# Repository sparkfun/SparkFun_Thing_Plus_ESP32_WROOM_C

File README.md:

SparkFun Thing Plus - ESP32 WROOM (USB-C)
========================================

*[SparkFun Thing Plus - ESP32 WROOM (USB-C) (WRL-20168)](https://www.sparkfun.com/products/20168)*

The [SparkFun Thing Plus - ESP32 WROOM (USB-C)](https://www.sparkfun.com/products/20168) is a comprehensive development platform for [Espressif's ESP32](https://espressif.com/en/products/hardware/esp32/overview). Thanks to the onboard ESP32 WROOM module, the SparkFun Thing Plus features 16MB of flash memory, 520kB of internal SRAM, an integrated 802.11 BGN WiFi transceiver and dual-mode Bluetooth capabilities, a JST connector to plug in a LiPo battery, a Qwiic connector, and 21 I/O pins. Add to that a rich set of peripherals ranging from capacitive touch sensors, Hall sensors, SD card interface, Ethernet, high-speed SPIs, UARTs, I2S, and I<sup>2</sup>C.

We took all the good from the original [ESP32 Thing Plus](https://www.sparkfun.com/products/15663) and sprinkled on some more. We upgraded to a USB-C connector that provides up to 2A of power, added a fuel gauge IC that will make sure you know your battery levels, included a NeoPixel (WS2812C) RGB LED is the perfect multi-status indicator, and threw a microSD connector on the back! Oh, and the new taller reset and boot buttons are **so** much easier to push! We even dedicated a voltage regulator to the Qwiic connector, which enables software power control to the Qwiic bus - great for low power logging!

Repository Contents
-------------------

* **[/Hardware](/Hardware/)** - KiCad design files (.kicad_sch, .kicad_pcb). Parts come from the [SparkFun KiCad Libraries](https://github.com/sparkfun/SparkFun-KiCad-Libraries)
* **[/Documents](/Documents/)** - Design notes: pin map, design calculations, BOM changes
* **[/Firmware](/Firmware/)** - Example sketches demonstrating extra peripherals

Documentation
--------------
* **[Hookup Guide](https://learn.sparkfun.com/tutorials/2353)** - Hookup guide for the ESP32 Thing Plus (USB-C).
* **[SparkFun Graphical Datasheets](https://github.com/sparkfun/Graphical_Datasheets)** -Graphical Datasheets for various SparkFun products.

Product Versions
----------------
* ESP32 Thing Plus (USB-C variant)
  * [WRL-20168](https://www.sparkfun.com/products/20168) - v5.0, ESP32-WROOM-32E-N16R2 module (16MB flash, 2MB PSRAM). Header RX moves to IO17 and TX to IO1 (UART0) because IO16 is used by the PSRAM. Design files moved from Eagle to KiCad.
  * [WRL-20168](https://www.sparkfun.com/products/20168) - v1.0, Initial Release
  * [SPX-18018](https://www.sparkfun.com/products/18018) - SparkX Release
* ESP32 Thing Plus
  * [WRL-17381](https://www.sparkfun.com/products/17381) (u.FL variant) - v1.0, Initial Release
  * [WRL-15663](https://www.sparkfun.com/products/15663)- v2.0, Slight hardware update that includes a 10&ohm; series resistor between VUSB and CP2102
  * [WRL-14689](https://www.sparkfun.com/products/14689)- v1.0, Initial Release

License Information
-------------------

This product is _**open source**_! 

Please review the LICENSE.md file for license information. 

If you have any questions or concerns on licensing, please contact technical support on our [SparkFun forums](https://forum.sparkfun.com/viewforum.php?f=152).

Distributed as-is; no warranty is given.

- Your friends at SparkFun.

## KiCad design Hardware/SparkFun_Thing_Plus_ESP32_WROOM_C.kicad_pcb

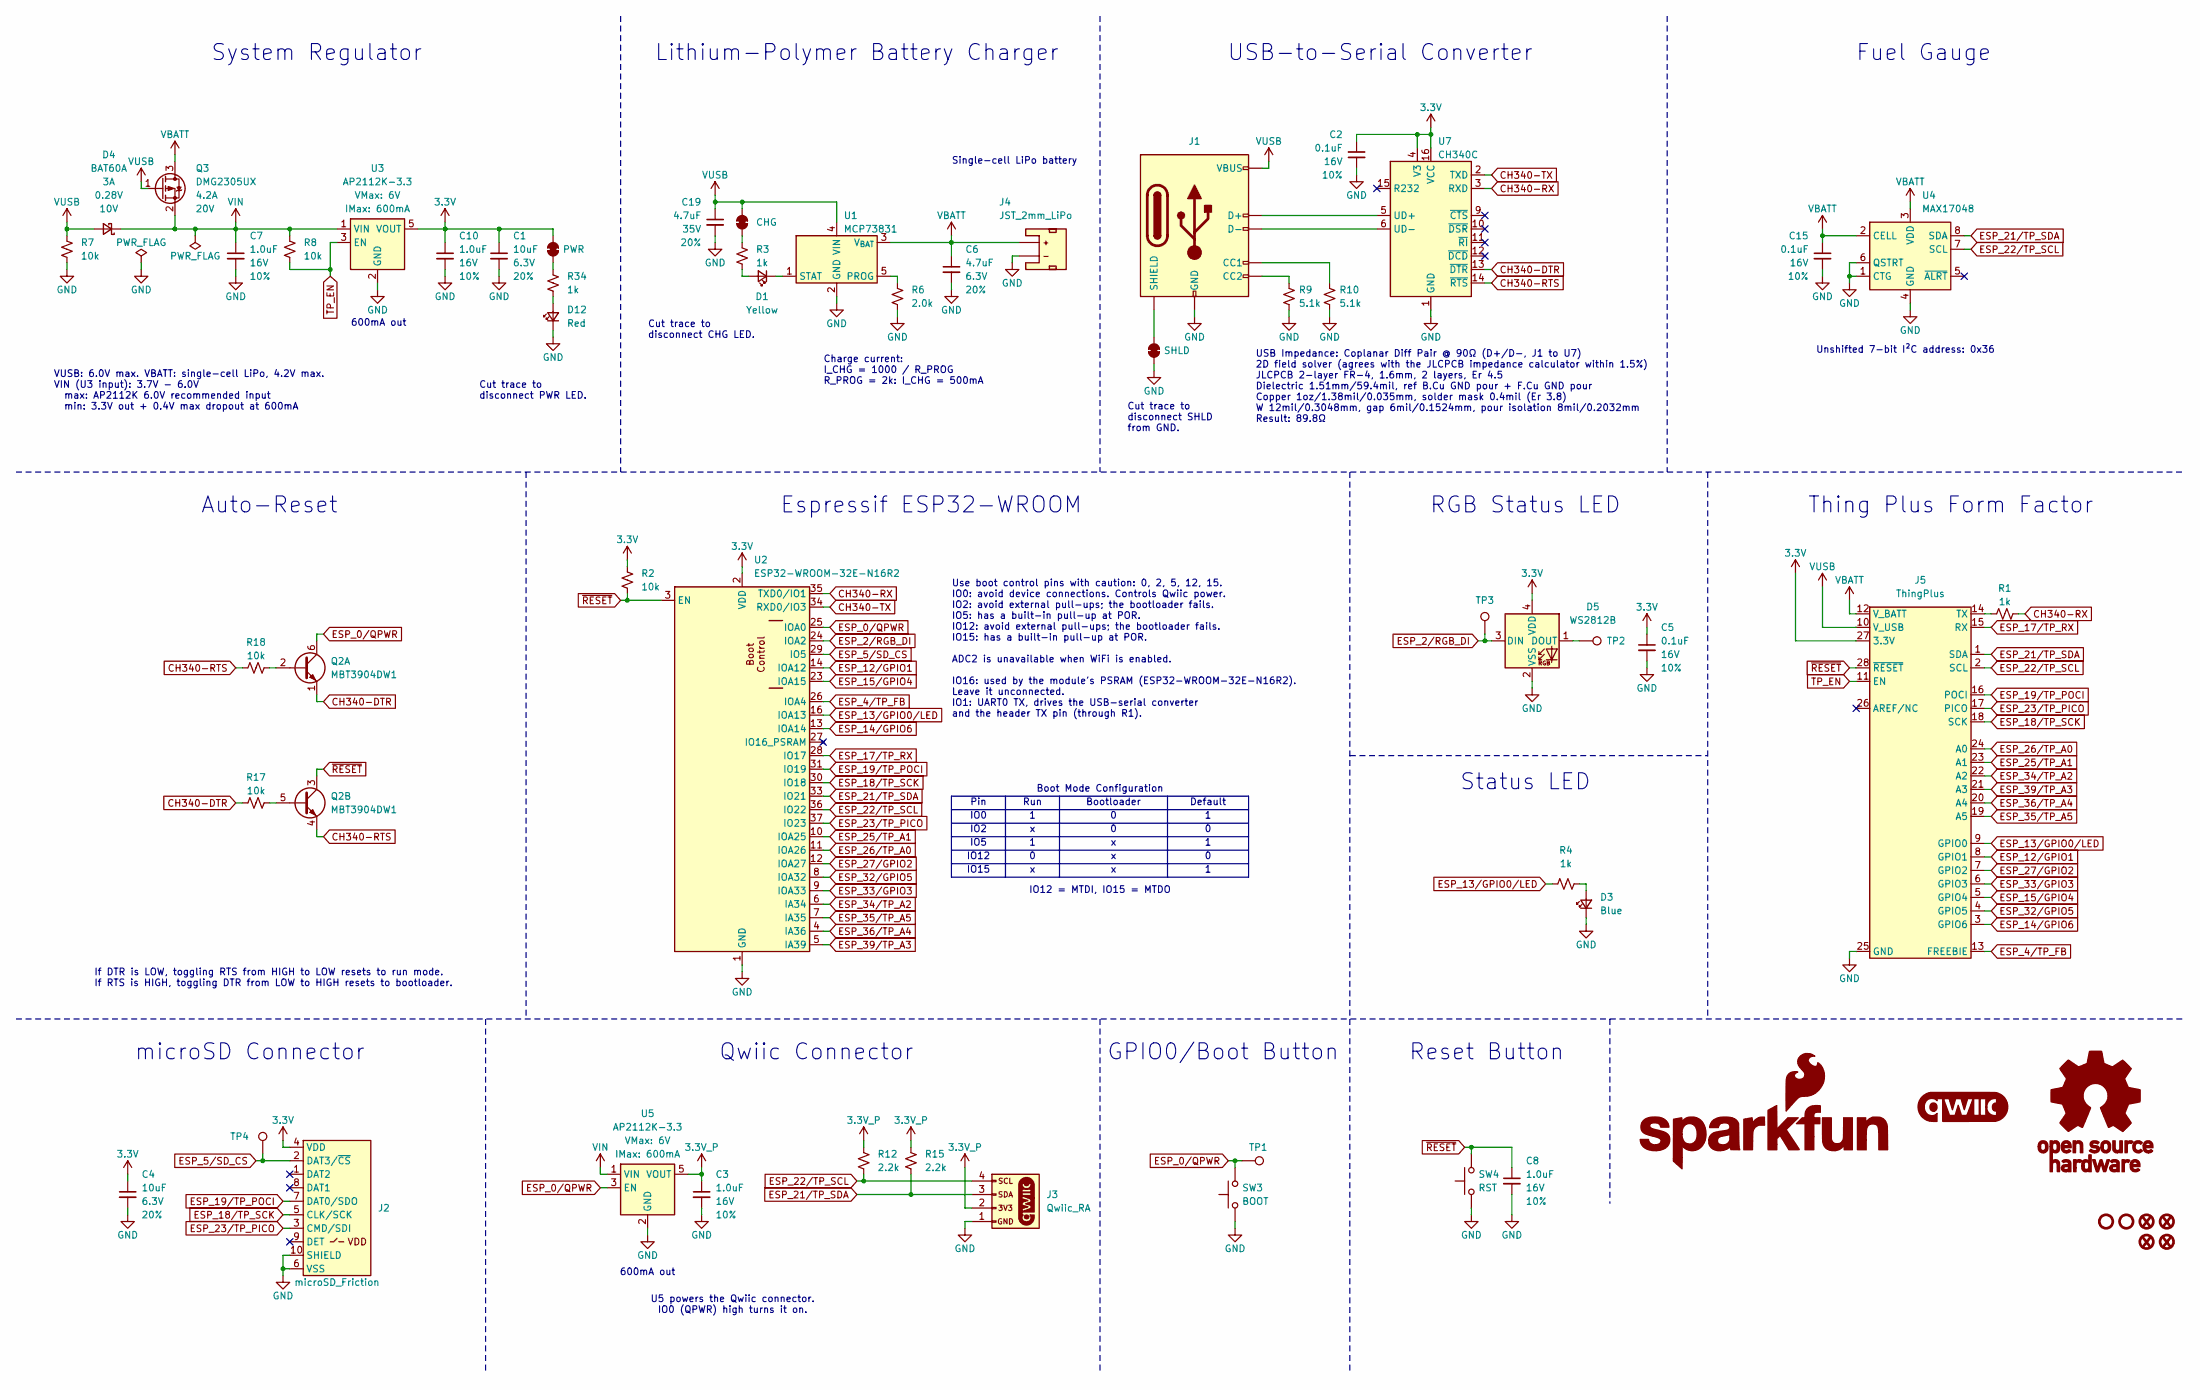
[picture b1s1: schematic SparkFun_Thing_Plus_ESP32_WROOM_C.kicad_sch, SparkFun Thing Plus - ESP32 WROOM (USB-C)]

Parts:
C1, C4: 10uF; C_0402_1005Metric; Voltage 6.3V; Tolerance 20%
C2, C5, C15: 0.1uF; C_0402_1005Metric; Voltage 16V; Tolerance 10%
C3, C7, C8, C10: 1.0uF; C_0402_1005Metric; Voltage 16V; Tolerance 10%
C6: 4.7uF; C_0402_1005Metric; Voltage 6.3V; Tolerance 20%
C19: 4.7uF; C_0603_1608Metric; Voltage 35V; Tolerance 20%
D1: Yellow; LED_0603_1608Metric_Yellow
D3: Blue; LED_0603_1608Metric_Blue
D4: BAT60A; SOD-323
D5: WS2812B; WS2812_2020
D12: Red; LED_0603_1608Metric_Red
FD1, FD2, FD3, FD4: Fiducial_0.5mm; Fiducial_0.5mm_Mask1mm
H1, H2: Standoff
J1: USB_C_Receptacle; USB-C_16
J2: microSD_Friction; microSD_Friction_Fit_Common
J3: Qwiic_RA; JST_1x04_P1.0mm_Horizontal_SMD
J4: JST_2mm_LiPo; JST_1x02_P2.0mm_Horizontal_SMD
J5: ThingPlus
JP1: PWR; Jumper_2_NC_Trace
JP2: CHG; Jumper_2_NC_Trace
JP3: SHLD; Jumper_2_NC_Trace
Q2: MBT3904DW1; SOT-363_SC-70-6
Q3: DMG2305UX; SOT23-3
R1, R3, R4, R34: 1k; R_0402_1005Metric
R2, R7, R8, R17, R18: 10k; R_0402_1005Metric
R6: 2.0k; R_0603_1608Metric
R9, R10: 5.1k; R_0402_1005Metric
R12, R15: 2.2k; R_0402_1005Metric
SW3: BOOT; Push_SMD_4.6x2.8mm_h2.5mm
SW4: RST; Push_SMD_4.6x2.8mm_h2.5mm
TP1, TP2, TP3, TP4: 0.75mm; TestPoint-0.75mm
U1: MCP73831; SOT23-5
U2: ESP32-WROOM-32E-N16R2; ESP32-WROOM-32D_Narrow
U3, U5: AP2112K-3.3; SOT23-5
U4: MAX17048; DFN-8_2x2mm_P0.5mm_EP1.2x0.8mm
U7: CH340C; SO-16

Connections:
3.3V: C1.1, C2.1, C4.1, C5.1, C10.1, D5.4 (VDD), J2.4 (VDD), J5.27 (3.3V), JP1.2 (B), R2.2, U2.2 (VDD), U3.5 (VOUT), U7.4 (V3), U7.16 (VCC)
3.3V_P: C3.1, J3.2, R12.2, R15.2, U5.5 (VOUT)
CH340-DTR: Q2.1 (E1), R17.1, U7.13 (~DTR)
CH340-RTS: Q2.4 (E2), R18.1, U7.14 (~RTS)
CH340-RX: R1.2, U2.35 (TXD0/IO1), U7.3 (RXD)
CH340-TX: U2.34 (RXD0/IO3), U7.2 (TXD)
ESP_0/QPWR: Q2.6 (C1), SW3.2, TP1.1 (1_1), U2.25 (IOA0), U5.3 (EN)
ESP_2/RGB_DI: D5.3 (DIN), TP3.1 (1_1), U2.24 (IOA2)
ESP_4/TP_FB: J5.13 (FREEBIE), U2.26 (IOA4)
ESP_5/SD_CS: J2.2 (DAT3/~CS), TP4.1 (1_1), U2.29 (IO5)
ESP_12/GPIO1: J5.8 (GPIO1), U2.14 (IOA12)
ESP_13/GPIO0/LED: J5.9 (GPIO0), R4.1, U2.16 (IOA13)
ESP_14/GPIO6: J5.3 (GPIO6), U2.13 (IOA14)
ESP_15/GPIO4: J5.5 (GPIO4), U2.23 (IOA15)
ESP_17/TP_RX: J5.15 (RX), U2.28 (IO17)
ESP_18/TP_SCK: J2.5 (CLK/SCK), J5.18 (SCK), U2.30 (IO18)
ESP_19/TP_POCI: J2.7 (DAT0/SDO), J5.16 (POCI), U2.31 (IO19)
ESP_21/TP_SDA: J3.3, J5.1 (SDA), R15.1, U2.33 (IO21), U4.8 (SDA)
ESP_22/TP_SCL: J3.4, J5.2 (SCL), R12.1, U2.36 (IO22), U4.7 (SCL)
ESP_23/TP_PICO: J2.3 (CMD/SDI), J5.17 (PICO), U2.37 (IO23)
ESP_25/TP_A1: J5.23 (A1), U2.10 (IOA25)
ESP_26/TP_A0: J5.24 (A0), U2.11 (IOA26)
ESP_27/GPIO2: J5.7 (GPIO2), U2.12 (IOA27)
ESP_32/GPIO5: J5.4 (GPIO5), U2.8 (IOA32)
ESP_33/GPIO3: J5.6 (GPIO3), U2.9 (IOA33)
ESP_34/TP_A2: J5.22 (A2), U2.6 (IA34)
ESP_35/TP_A5: J5.19 (A5), U2.7 (IA35)
ESP_36/TP_A4: J5.20 (A4), U2.4 (IA36)
ESP_39/TP_A3: J5.21 (A3), U2.5 (IA39)
GND: C1.2, C2.2, C3.2, C4.2, C5.2, C6.2, C7.2, C8.2, C10.2, C15.2, C19.2, D3.1 (K), D5.2 (VSS), D12.1 (K), J1.GND, J2.6 (VSS), J2.10 (SHIELD), J3.1, J4.1 (-), J5.25 (GND), JP3.1 (A), R6.1, R7.1, R9.1, R10.1, SW3.1, SW4.1, U1.2 (GND), U2.1 (GND), U2.15 (GND), U2.38 (GND), U2.49.1 (GND), U2.49.2 (GND), U2.49.3 (GND), U2.49.4 (GND), U2.49.5 (GND), U2.49.6 (GND), U2.49.7 (GND), U2.49.8 (GND), U2.49.9 (GND), U3.2 (GND), U4.1 (CTG), U4.4 (GND), U4.6 (QSTRT), U4.9 (GND), U5.2 (GND), U7.1 (GND)
unnamed: D1.2 (A), R3.2
unnamed: D1.1 (K), U1.1 (STAT)
unnamed: D3.2 (A), R4.2
unnamed: D5.1 (DOUT), TP2.1 (1_1)
unnamed: D12.2 (A), R34.2
unnamed: J1.A5 (CC1), R10.2
unnamed: J1.B5 (CC2), R9.2
unnamed: J1.S (SHIELD), JP3.2 (B)
unnamed: J5.14 (TX), R1.1
unnamed: JP1.1 (A), R34.1
unnamed: JP2.1 (A), R3.1
unnamed: Q2.2 (B1), R18.2
unnamed: Q2.5 (B2), R17.2
unnamed: R6.2, U1.5 (PROG)
unnamed: J1.A6 (D+), J1.B6 (D+), U7.5 (UD+)
unnamed: J1.A7 (D-), J1.B7 (D-), U7.6 (UD-)
TP_EN: J5.11 (EN), R8.2, U3.3 (EN)
VBATT: C6.1, C15.1, J4.2 (+), J5.12 (V_BATT), Q3.3 (D), U1.3 (V_{BAT}), U4.2 (CELL), U4.3 (VDD)
VIN: C7.1, D4.1 (K), Q3.2 (S), R8.1, U3.1 (VIN), U5.1 (VIN)
VUSB: C19.1, D4.2 (A), J1.VBUS, J5.10 (V_USB), JP2.2 (B), Q3.1 (G), R7.2, U1.4 (VIN)
~RESET: C8.1, J5.28 (~RESET), Q2.3 (C2), R2.1, SW4.2, U2.3 (EN)

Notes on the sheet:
600mA out
Boot Mode Configuration
If DTR is LOW, toggling RTS from HIGH to LOW resets to run mode. If RTS is HIGH, toggling DTR from LOW to HIGH resets to bootloader.
Cut trace to disconnect PWR LED.
Cut trace to disconnect CHG LED.
Single-cell LiPo battery
Status LED
Default
IO12 = MTDI, IO15 = MTDO
VUSB: 6.0V max. VBATT: single-cell LiPo, 4.2V max. VIN (U3 input): 3.7V - 6.0V max: AP2112K 6.0V recommended input min: 3.3V out + 0.4V max dropout at 600mA
IO0
Lithium-Polymer Battery Charger
Cut trace to disconnect SHLD from GND.
Auto-Reset
IO2
Fuel Gauge
U5 powers the Qwiic connector. IO0 (QPWR) high turns it on.
USB-to-Serial Converter
System Regulator
IO15
IO12
Espressif ESP32-WROOM
Unshifted 7-bit I²C address: 0x36
RGB Status LED
Thing Plus Form Factor
Pin
Bootloader
Run
Use boot control pins with caution: 0, 2, 5, 12, 15. IO0: avoid device connections. Controls Qwiic power. IO2: avoid external pull-ups; the bootloader fails. IO5: has a built-in pull-up at POR. IO12: avoid external pull-ups; the bootloader fails. IO15: has a built-in pull-up at POR. ADC2 is unavail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
Charge current: I_CHG = 1000 / R_PROG R_PROG = 2k: I_CHG = 500mA
Reset Button
GPIO0/Boot Button
Qwiic Connector
IO5
USB Impedance: Coplanar Diff Pair @ 90Ω (D+/D-, J1 to U7) 2D field solver (agrees with the JLCPCB impedance calculator within 1.5%) JLCPCB 2-layer FR-4, 1.6mm, 2 layers, Er 4.5 Dielectric 1.51mm/59.4mil, ref B.Cu GND pour + F.Cu GND pour Copper 1oz/1.38mil/0.035mm, solder mask 0.4mil (Er 3.8) W 12m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
microSD Connector

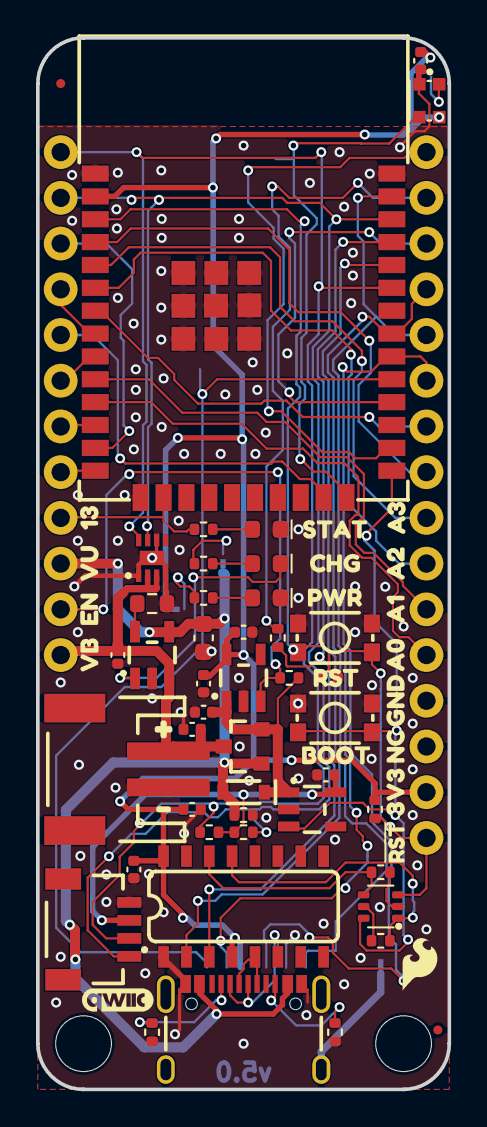
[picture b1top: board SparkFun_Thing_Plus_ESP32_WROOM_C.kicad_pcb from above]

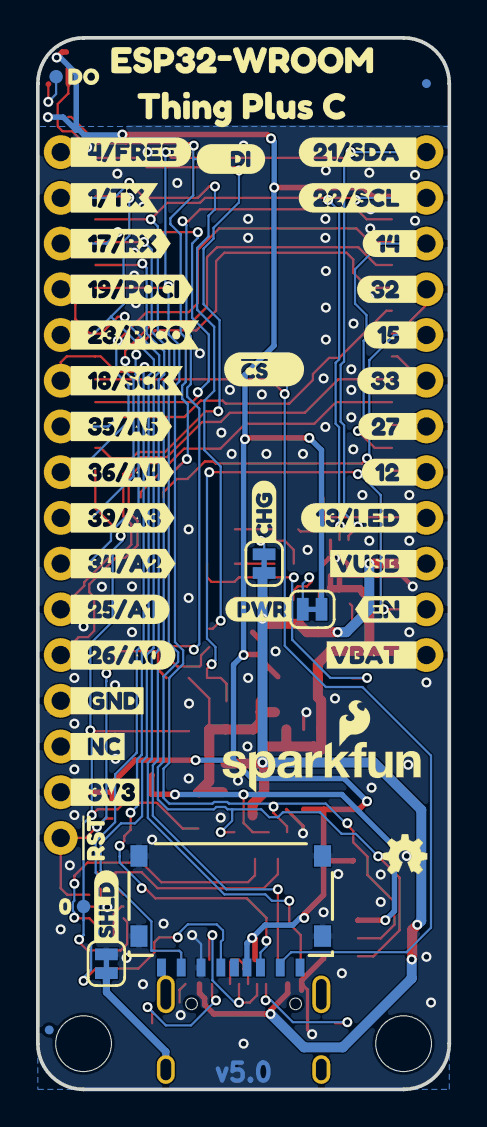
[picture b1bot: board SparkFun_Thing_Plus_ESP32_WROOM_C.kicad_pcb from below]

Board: 2 copper layers, 22.9 x 58.4 mm, 119 parts (50 on the bottom side), 51 nets.

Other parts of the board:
LOGO1: LOGO; SparkFun_Logo_11mm
LOGO2: Val**; OSHW_Logo_2.5mm
LOGO3: Flame; SparkFun_Flame_2.5mm_Mask
LOGO4: LOGO; qwiic_4mm
U$12: Flame; SparkFun_Flame_3mm
kibuzzard-0C7E9708: G***; kibuzzard-0C7E9708
kibuzzard-0D77A6BB: G***; kibuzzard-0D77A6BB
kibuzzard-3BF3E0AD: G***; kibuzzard-3BF3E0AD
kibuzzard-6AE2BB3D: G***; kibuzzard-6AE2BB3D
kibuzzard-6AE2BB5D: G***; kibuzzard-6AE2BB5D
kibuzzard-6AE2BB58: G***; kibuzzard-6AE2BB58
kibuzzard-6AE2BB62: G***; kibuzzard-6AE2BB62
kibuzzard-6B1B6006: G***; kibuzzard-6B1B6006
kibuzzard-6B008A31: G***; kibuzzard-6B008A31
kibuzzard-7B7C629F: G***; kibuzzard-7B7C629F
kibuzzard-7B780335: G***; kibuzzard-7B780335
kibuzzard-8AF7A47A: G***; kibuzzard-8AF7A47A
kibuzzard-8CA9E534: G***; kibuzzard-8CA9E534
kibuzzard-8CD6BF82: G***; kibuzzard-8CD6BF82
kibuzzard-8DD2FE29: G***; kibuzzard-8DD2FE29
kibuzzard-9ECC0383: G***; kibuzzard-9ECC0383
kibuzzard-20D9B321: G***; kibuzzard-20D9B321
kibuzzard-35C6CBE8: G***; kibuzzard-35C6CBE8
kibuzzard-37F5297F: G***; kibuzzard-37F5297F
kibuzzard-47F25198: G***; kibuzzard-47F25198
kibuzzard-291EFBC7: G***; kibuzzard-291EFBC7
kibuzzard-0359C089: G***; kibuzzard-0359C089
kibuzzard-392BC215: G***; kibuzzard-392BC215
kibuzzard-422EFA4A: G***; kibuzzard-422EFA4A
kibuzzard-618B0B87: G***; kibuzzard-618B0B87
kibuzzard-4355F0EE: G***; kibuzzard-4355F0EE
kibuzzard-5584D9FD: G***; kibuzzard-5584D9FD
kibuzzard-8933AD9A: G***; kibuzzard-8933AD9A
kibuzzard-9751AE1C: G***; kibuzzard-9751AE1C
kibuzzard-607611B0: G***; kibuzzard-607611B0
kibuzzard-0613341D: G***; kibuzzard-0613341D
kibuzzard-788367CB: G***; kibuzzard-788367CB
kibuzzard-23275438: G***; kibuzzard-23275438
kibuzzard-A6F82761: G***; kibuzzard-A6F82761
kibuzzard-AA29B278: G***; kibuzzard-AA29B278
kibuzzard-AF08375C: G***; kibuzzard-AF08375C
kibuzzard-B5AF6DC0: G***; kibuzzard-B5AF6DC0
kibuzzard-B80965C8: G***; kibuzzard-B80965C8
kibuzzard-BAC9EE9C: G***; kibuzzard-BAC9EE9C
kibuzzard-BATTN: G***; kibuzzard-BATTN
kibuzzard-BATTP: G***; kibuzzard-BATTP
kibuzzard-C2E00F98: G***; kibuzzard-C2E00F98
kibuzzard-C4F3B311: G***; kibuzzard-C4F3B311
kibuzzard-CD4FB525: G***; kibuzzard-CD4FB525
kibuzzard-CDD75B72: G***; kibuzzard-CDD75B72
kibuzzard-D6DEC2C9: G***; kibuzzard-D6DEC2C9
kibuzzard-DA8C56B8: G***; kibuzzard-DA8C56B8
kibuzzard-DAF9EF57: G***; kibuzzard-DAF9EF57
kibuzzard-EA4B9891: G***; kibuzzard-EA4B9891
kibuzzard-EDC126A3: G***; kibuzzard-EDC126A3
kibuzzard-F3EADD72: G***; kibuzzard-F3EADD72
kibuzzard-FF687C2B: G***; kibuzzard-FF687C2B
kibuzzard-TP1: G***; kibuzzard-TP1
kibuzzard-TP2: G***; kibuzzard-TP2
kibuzzard-TP3: G***; kibuzzard-TP3
kibuzzard-TP4: G***; kibuzzard-TP4

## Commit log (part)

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2022-05-18 Pulled in files from SpX repo.
    Pulled in all the files from the SpX repo except production files and the old PDF schematic.
2022-05-19 Renamed schematics, replaced parts with sfe lib parts.
2022-05-19 All parts are now from SFE libs.
2022-05-19 Placed all new components, pinned out PTHs.
2022-05-19 End of day commit, placed uSD conn and began routing.
2022-05-20 Initial reroute complete.
2022-05-23 Completed Board update pre-DR.
2022-05-25 Completed updates post DR.
    Schematic:
    Change all text to vector, 8%
    Add row lines to boot mode table
    Add NC jumper on USB-C shield.
    Change 0.1u cap to 10u next to uSD.
    Update uSD device to pull in newest changes to keepout.
2022-05-26 Update post DR changes.
    Minor movement edits.
2022-05-26 Increase board length to sit on 0.05" grid.
    Originally had only increased by 0.01", however was told that customers prefer 0.05" increments for designing around.
2022-05-26 Added 7-bit I2C address text.
2022-05-26 Panelized for production review.
2022-05-26 Upload temp panel for Kasey.
2022-05-26 Updated panel
2022-05-26 Cammed for ordering reds.
2022-06-29 Update BOM for cap mismatch.
    Accidentally placed C4/C5 in the wrong spot. Made the change in schematic so no board reorder is necessary.
2022-06-29 Add new sketches.
    Add test sketches.
2022-07-15 Update README.md
    Clean up description and remove TBRs
    Add documentation and product version sections
    Update links
    Still needs product image
2022-08-03 Add mkdocs files
    Initial commit for documentation with mkdocs
2022-08-03 Add documentation assets
    Component datasheets
    Images for hookup guide
    Graphical datasheet files
    Add hardware assets:
    - pdfs for board dimensions, schematic, and graphical datasheet
    - .zip of eagle files (test if compatible with documentation)
2022-08-03 Update README.md
    link asset files
    add badges for issues, docs build (test), twitter
2022-08-03 Move board files
    Links break in documentation build
    Files must be within `docs` folder
2022-08-03 Index file required
    renamed introduction to index
2022-08-03 Update product documentation
    - added missing files for documentation
    - re-index files:
    - replaced introduction with index file (required)
    - replaced resources and broke down into smaller files
    - updated files to fix most formatting issues and html breakdowns
    - hardware overview (still in progress)
2022-08-09 Update graphical datasheet
    Fix error in voltage range for ESP32 module
    Should be 3.0V - 3.6V
2022-08-09 Move header to mkdocs.yml
    Removes <H1> header from markdown files
    Adds header to nav menu from mkdocs.yml
2022-08-09 Add badges
    Add badges for
    - Docs build
    - Issues
    - PR/Contributors
    - License
    - Twitter
2022-08-09 Rename file
    Rename file to resources.md
2022-08-09 Update hardware_overview.md
    Update Arduino link - documentation changed and linked to a different page
2022-08-09 Fix macros issue
    Replace columns with tables
    Replace div well with annotations
    Replace tutorial macro with img/hyperlink
    Replace video macro with embedded video
2022-08-09 Update getting_started.md
    Make indentations consistent
2022-08-09 Update hardware_overview.md
    Fix link
    Fix table spacing
    Fix annotation
    Fix table entries
2022-08-09 Create hardware_overview-tabs_version.md
    Keep back up of hardware overview section with tabs
2022-08-11 Rename and remove images
    Removed unnecessary images
    Renamed images to make more sense
2022-08-11 Update asset links
    Update docs to use local files in the repo
2022-08-11 Update sparkfun_pages.md
    Remove link to GitHub repository... documentation already in repo
2022-08-11 Add product image
    Add default product image
2022-08-11 Update index.md
    Add link to product
2022-08-11 Update documentation
    Fix bold in italics issue (can't use stars for italics)
    Set image widths
    - 500px for outside resources (product or tutorial pages)
    - 400px for internal resources (example figures or product annotations)
    Fix image links
    - html needs full link; unlike the markdown
2022-08-11 Update contribute.md
    Fix typo
2022-08-11 Update mkdocs.yml
    Set build to branch
2022-08-16 Fix spelling and grammar
    Spell Check
    Grammar
2022-08-16 Rename Files
    Renamed resource files
2022-08-18 Update README.md
    Add product image
    Fix product description
    Link folders
2022-08-18 Update README.md
    Fix product link for image
2022-08-18 Remove Fritzing link
    Did not make a Fritzing diagram for this product
2022-08-18 Fix Header
    Move header into mkdocs.yml
2022-08-18 Update README.md
    Remove "REPLACE ME" text
    Reorganize and fix repository content links
    Remove fritzing link - none made
2022-08-18 Fix images
    Link images with relative file paths
    Centering in tables <td align="center">
2022-08-18 Update README.md
    Link GitHub pages documentation
2022-08-18 Add product video
    Embedded product video
2022-08-18 Fix badges
    Move badges into text area and not in headers
2022-08-18 Move badge
    Oops... put badge in wrong text area
2022-08-18 Fix video link
    Replace placeholder link
2022-08-19 Update index.md
    Link product image to product page
2022-11-09 Update README.md
    Repo should contain MIT license for hardware/code
    CC license is for the docs
2022-11-09 Fix typos
    Fixes spelling and grammatical errors
2022-11-09 Update mkdocs.yml
    Rename Tabs/Titles
    - Product Manual -> Hookup Guide
    - <Product Name> -> Product Description
    - Contribution/Issues -> Issues/Pull Requests
2023-02-01 Consolidate resource info
    Consolidate resource information into a single file
2023-02-01 Update mkdocs.yml
    Add comments and move page info to top
2023-02-01 consolidate product info
2023-02-01 Add hard copy
    Provides users with option to view guide as a single page
    Links generated pdf of webpage (beta)
2023-02-01 add pdf rendering
2023-02-01 Custom Admonitions
2023-02-01 Update mkdocs.yml
    Add light/dark theme button
2023-02-01 Update mkdocs.yml
    move troubleshooting tips into support tab
2023-02-01 Update mkdocs.yml
    add social icon and favicon
2023-02-01 Add new page features
2023-02-01 Enable plugins
    Add installation for plugins
2023-02-01 fix hard copy stuff
    move github issue/commit files
    update links
2023-02-01 enable all plugins
    test build
2023-02-01 disable revision date
2023-02-01 update workflow
    test enable insiders build
2023-02-01 Revert "update workflow"
    This reverts commit 8af1f0109f0fd36de005d2ef8fa513474b9bacdd.
2023-02-01 update workflow
2023-02-02 Update mkdocs.yml
    update versions
2023-02-02 Update mkdocs.yml
    Update publish action: https://squidfunk.github.io/mkdocs-material/publishing-your-site/#with-github-actions
2023-02-02 remove features
    no committers or insiders
2023-02-02 test workflow
2023-02-02 remove build
2023-02-02 test
2023-02-02 move monorepo
2023-02-02 re-enable pdf
2023-02-02 insiders
2023-02-02 enable overrides
2023-02-15 Update datasheet
    New datasheet version - removes hall effect sensor info
2023-02-15 Add README files
    Change permalink icon
2023-02-21 Update mkdocs.yml
    Fix light/dark mode annotation
2023-02-21 Use figure elements
    Switch to figure elements for images
2023-02-21 Update Qwiic Logo
    Use new Qwiic logo
2023-02-21 Update copyright info
2023-02-21 Update PDF generation
    Remove subtitle and debug
2023-02-21 Update mkdocs.yml
    Remove easter egg
2023-02-21 Update Admonitions
    Use more than just the note admonition
2023-02-21 Update Docs
    Fix grammar/typos
    Sound more friendly
2023-02-21 Update tables
2023-02-21 Markdown updates
    Convert from html to markdown
2023-02-21 Update to tabs
2023-02-21 Update graphical datasheet image
    White background to be compatible with dark theme
2023-02-21 Add readme
2023-02-22 Update mkdocs.yml
    Fix product link and re-enable plugins
2023-03-22 Rename folder
2023-03-22 Update README.md
    link to release tag
2023-03-22 Update index.md
    Update to new standard
2023-03-22 Deployed 5dcb612 with MkDocs version: 1.4.2
2023-05-12 Update MAX17048_FuelGauge.ino
    Set the right adress
2023-06-21 BUGFIX: SD Card Mount Error on Thing Plus C
2023-07-19 Swap VREG IC
